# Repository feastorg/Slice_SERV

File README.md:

<div align="center">
  <!-- Title: -->
  
  <h2><a href="https://github.com/uwo-fast/Slice_SERV"> SERV Slice </a></h2>
  <!-- Labels: -->
  <!-- First row: -->

  <a href="https://certification.oshwa.org/">
    
    <!-- img src="https://img.shields.io/badge/OSHWA-Certified-darkgreen?style=flat-square" height="20" alt="OSHWA" -->       <!-- img src="https://img.shields.io/badge/OSHWA-Pending-darkorange?style=flat-square" height="20" alt="OSHWA" -->
  </a>

  <!-- Second row: -->
  <br>

  <!-- Short description: -->
  <h3>Servo Motor Control Slice for BREAD.</h3>
</div>

## Introduction
[Provide a brief introduction to the project, including the motivation and goals. Explain the significance and context of the research.]

## Project Overview
[Describe the project in more detail. This section can be split into subsections if necessary.]

## Installation
[Provide instructions for installing any necessary software or hardware components.]

## Usage
[Explain how to use the project. Include examples and screenshots if applicable.]

### Basic Usage
[Provide basic usage instructions.]

### Advanced Usage
[Provide advanced usage instructions, including any optional features or configurations.]

## Documentation
[Link to the detailed documentation if available. Provide instructions on how to access and navigate the documentation.]

## Contributing
[Explain how others can contribute to the project. Include guidelines for submitting issues, pull requests, and any coding standards.]

### Code of Conduct
[Link to the project's code of conduct if available.]

## License
[State the license under which the project is distributed. Include a link to the full license text.]

## Acknowledgements
[Acknowledge any contributors, collaborators, funding sources, or organizations that supported the project.]

## Contact
[Provide contact information for the project maintainer(s) or lead researcher(s). Include an email address or a link to a contact form.]

---

<div align="center">
  
</div>

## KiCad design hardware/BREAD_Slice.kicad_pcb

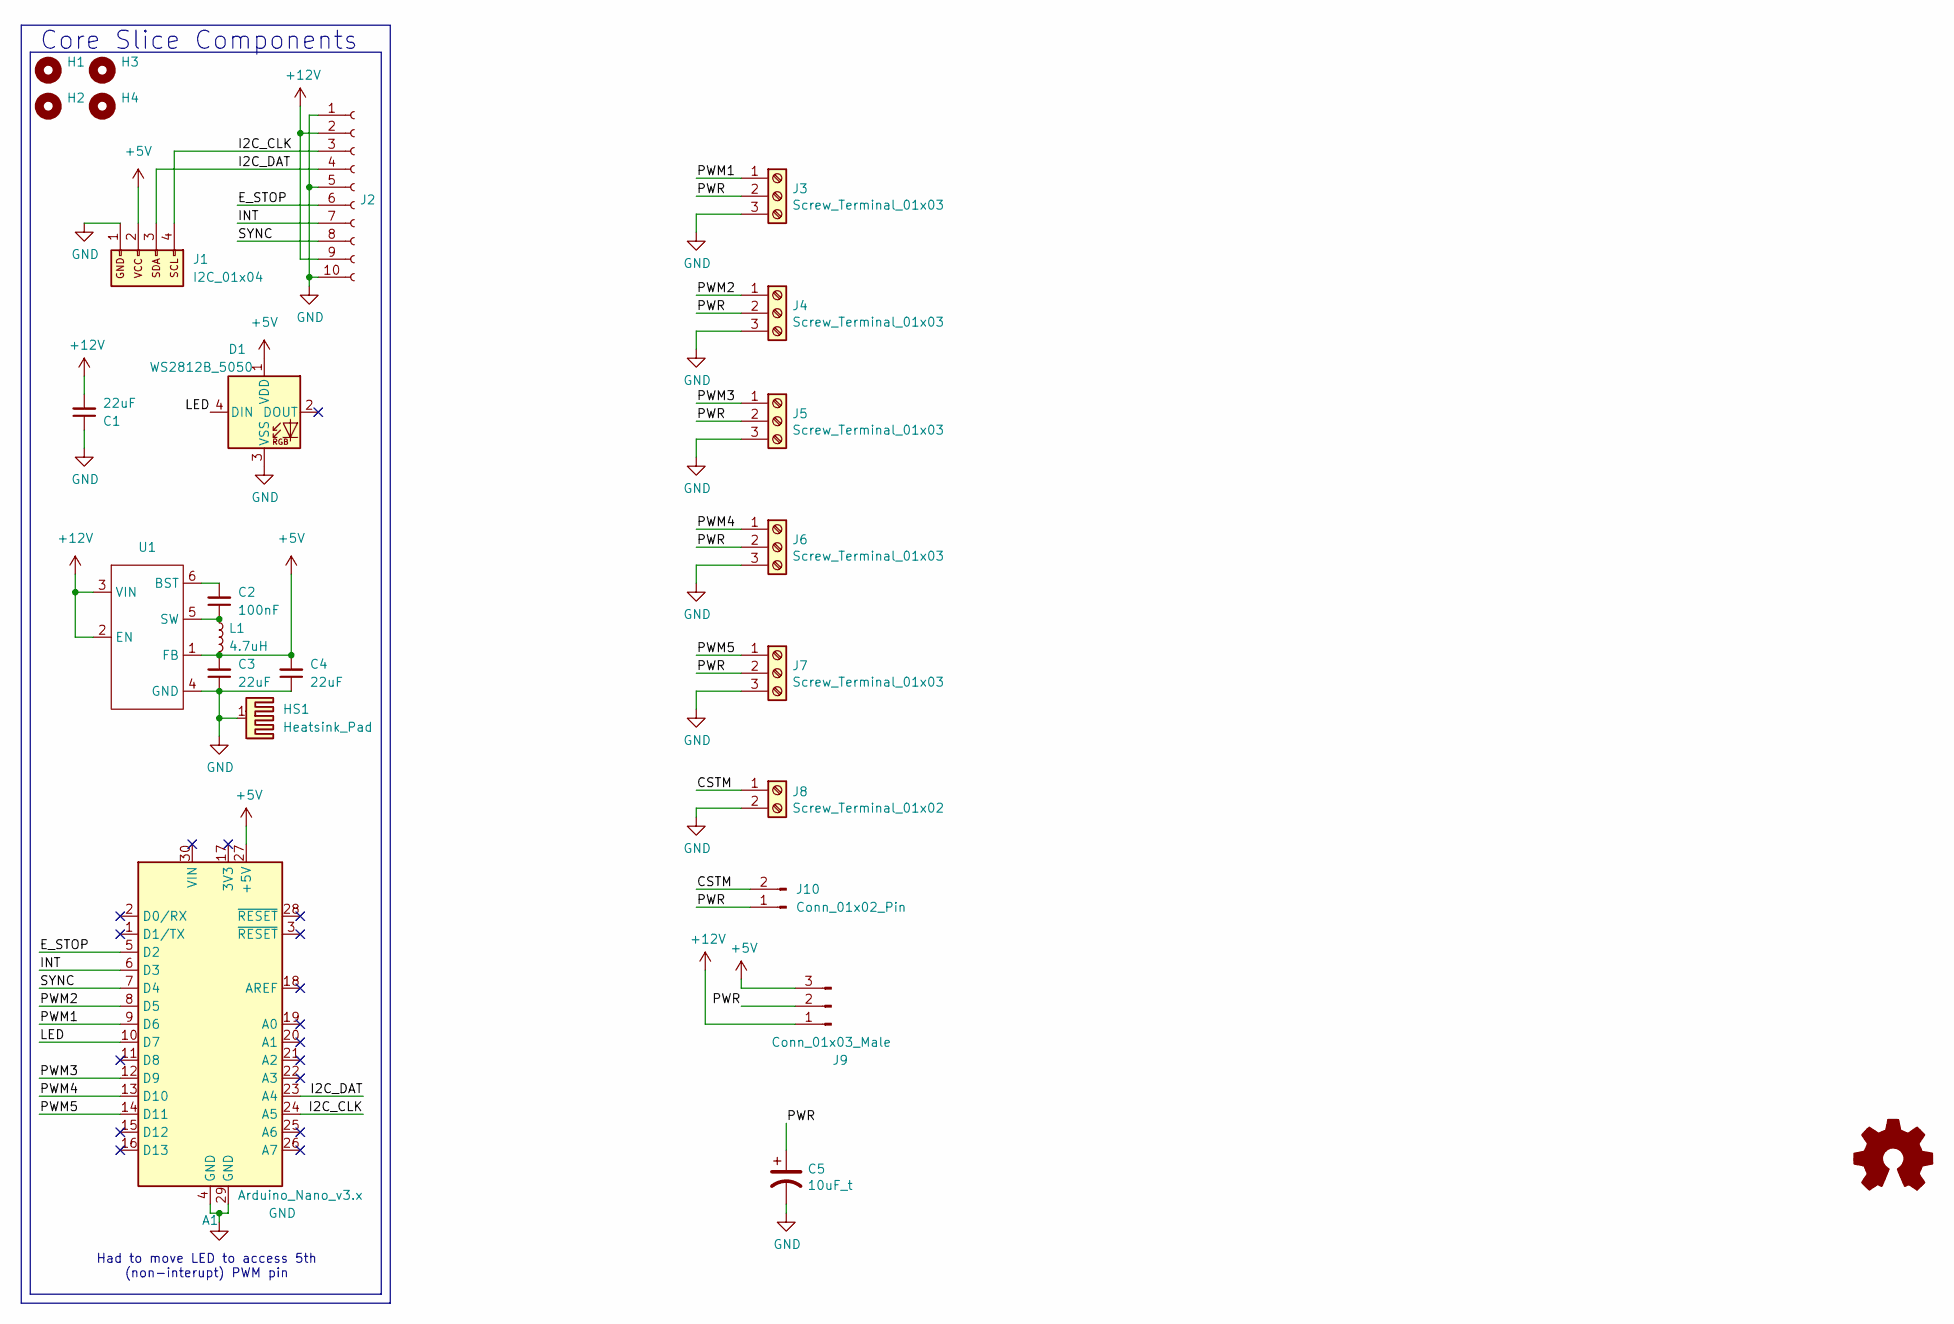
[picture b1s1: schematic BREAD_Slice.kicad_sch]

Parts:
A1: Arduino_Nano_v3.x; Arduino_Nano
C1, C3, C4: 22uF; C_1206_3216Metric
C2: 100nF; C_1206_3216Metric
C5: 10uF_t; C_2220_5750Metric_Pad1.97x5.40mm_HandSolder; Part # T491C106K025AT
D1: WS2812B_5050; WS2812-5050-4PIN
H1, H2, H3, H4: MountingHole; MountingHole_5mm
HS1: Heatsink_Pad; Thermal_Pad
J1: I2C_01x04; JST_SH_SM04B-SRSS-TB_1x04-1MP_P1.00mm_Horizontal
J2: Conn_01x10_Female; PinSocket_1x10_P2.54mm_Horizontal
J3, J4, J5, J6, J7: Screw_Terminal_01x03; TerminalBlock_Phoenix_MPT-0,5-3-2.54_1x03_P2.54mm_Horizontal
J8: Screw_Terminal_01x02; TerminalBlock_Phoenix_MPT-0,5-2-2.54_1x02_P2.54mm_Horizontal
J9: Conn_01x03_Male; PinSocket_1x03_P2.54mm_Vertical
J10: Conn_01x02_Pin; PinSocket_1x02_P2.54mm_Vertical
L1: 4.7uH; L_1210_3225Metric
U1: TSOT-23-6

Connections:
+5V: A1.27 (+5V), C3.2, C4.2, D1.1 (VDD), J1.2, J9.3, L1.2, U1.1 (FB)
+12V: C1.2, J2.2, J2.9, J9.1, U1.2 (EN), U1.3 (VIN)
/CSTM: J8.1, J10.2
/E_STOP: A1.5 (D2), J2.6
/I2C_CLK: A1.24 (A5), J1.4, J2.3
/I2C_DAT: A1.23 (A4), J1.3, J2.4
/INT: A1.6 (D3), J2.7
/LED: A1.10 (D7), D1.4 (DIN)
/PWM1: A1.9 (D6), J3.1
/PWM2: A1.8 (D5), J4.1
/PWM3: A1.12 (D9), J5.1
/PWM4: A1.13 (D10), J6.1
/PWM5: A1.14 (D11), J7.1
/PWR: C5.1, J3.2, J4.2, J5.2, J6.2, J7.2, J9.2, J10.1
/SYNC: A1.7 (D4), J2.8
GND: A1.4 (GND), A1.29 (GND), C1.1, C3.1, C4.1, C5.2, D1.3 (VSS), HS1.1, J1.1, J2.1, J2.5, J2.10, J3.3, J4.3, J5.3, J6.3, J7.3, J8.2, U1.4 (GND)
unnamed: C2.2, U1.6 (BST)
unnamed: C2.1, L1.1, U1.5 (SW)

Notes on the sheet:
Had to move LED to access 5th (non-interupt) PWM pin
Core Slice Components

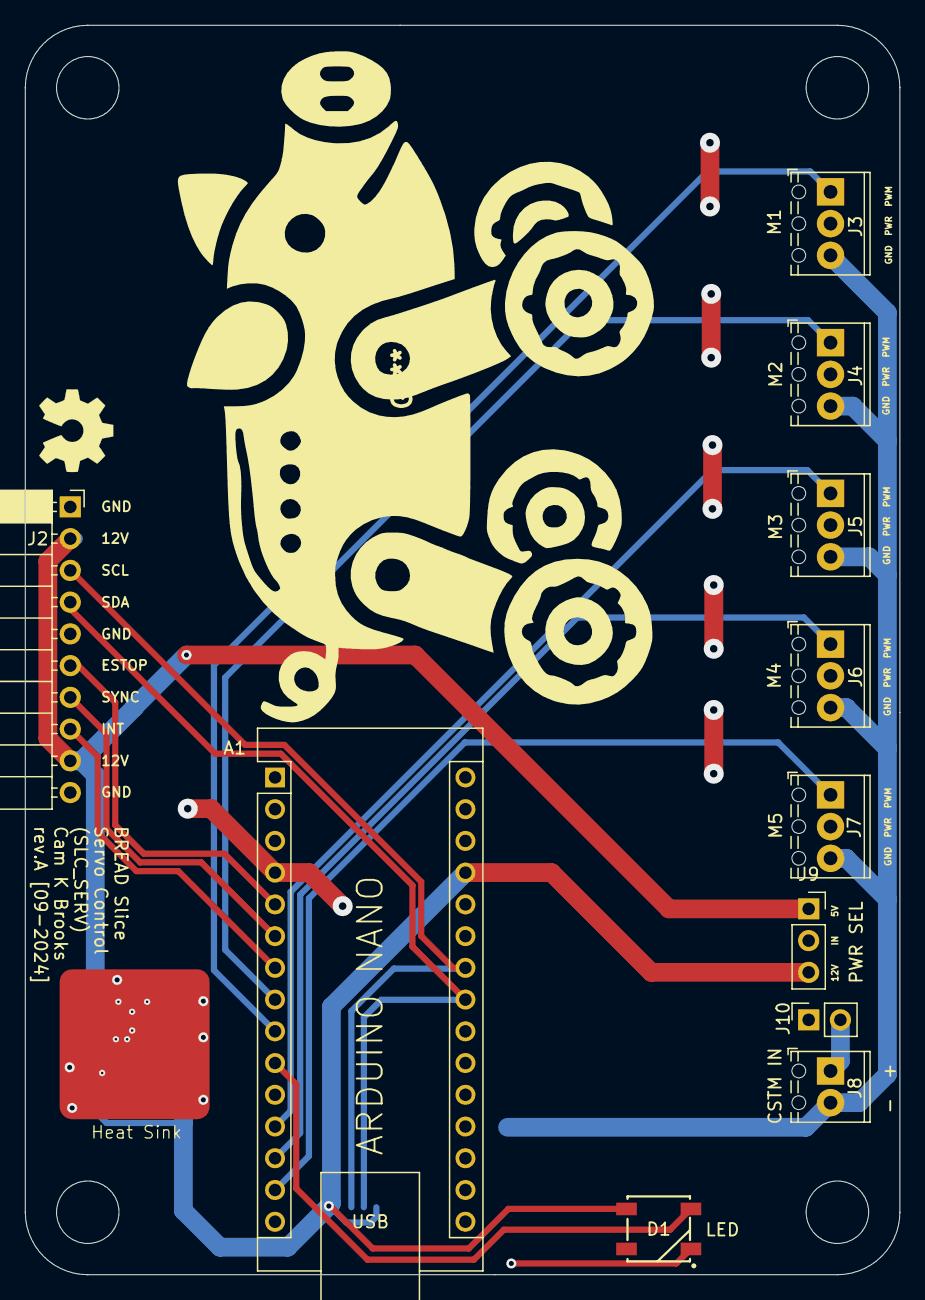
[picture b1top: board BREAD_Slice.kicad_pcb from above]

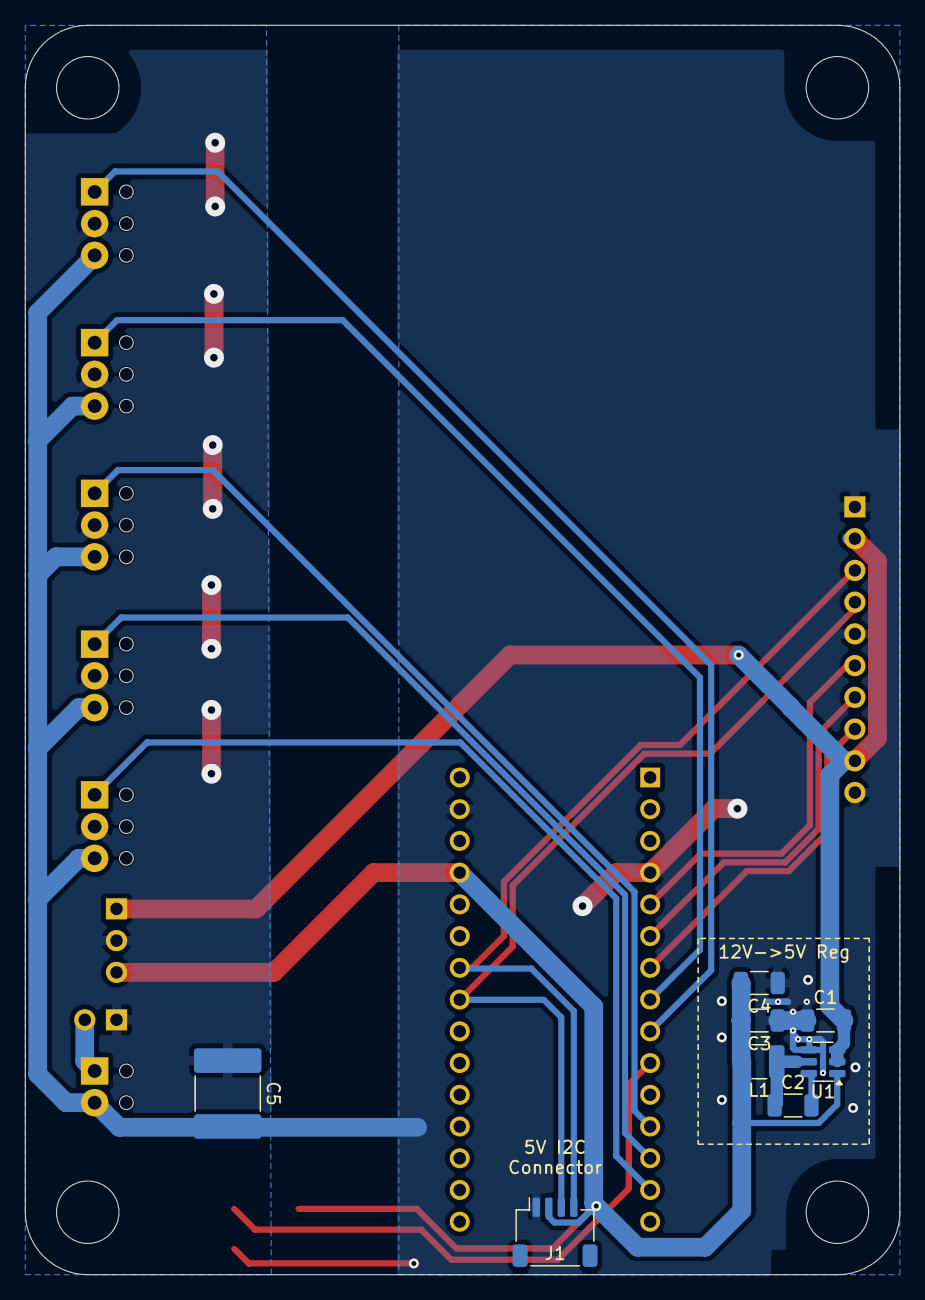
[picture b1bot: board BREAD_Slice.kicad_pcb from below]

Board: 2 copper layers, 70.0 x 100.0 mm, 25 parts (8 on the bottom side), 18 nets.

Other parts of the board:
Logo1: Logo_Open_Hardware_Small; OSHW-Symbol_6.7x6mm_SilkScreen

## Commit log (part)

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2024-09-13 changed custom selection method to be correct and offer 5V, new BREAD core
2024-09-13 removed old hardware folder
2024-09-30 JLCPCB order rev-A
2026-05-20 Add slice.yaml manifest (schema v1.0)
2026-05-24 Add KiBot/docs pipeline
2026-05-24 Update TODO with CI findings
2026-05-24 Standardize TODO.md with Pass 1/Pass 2 structure
